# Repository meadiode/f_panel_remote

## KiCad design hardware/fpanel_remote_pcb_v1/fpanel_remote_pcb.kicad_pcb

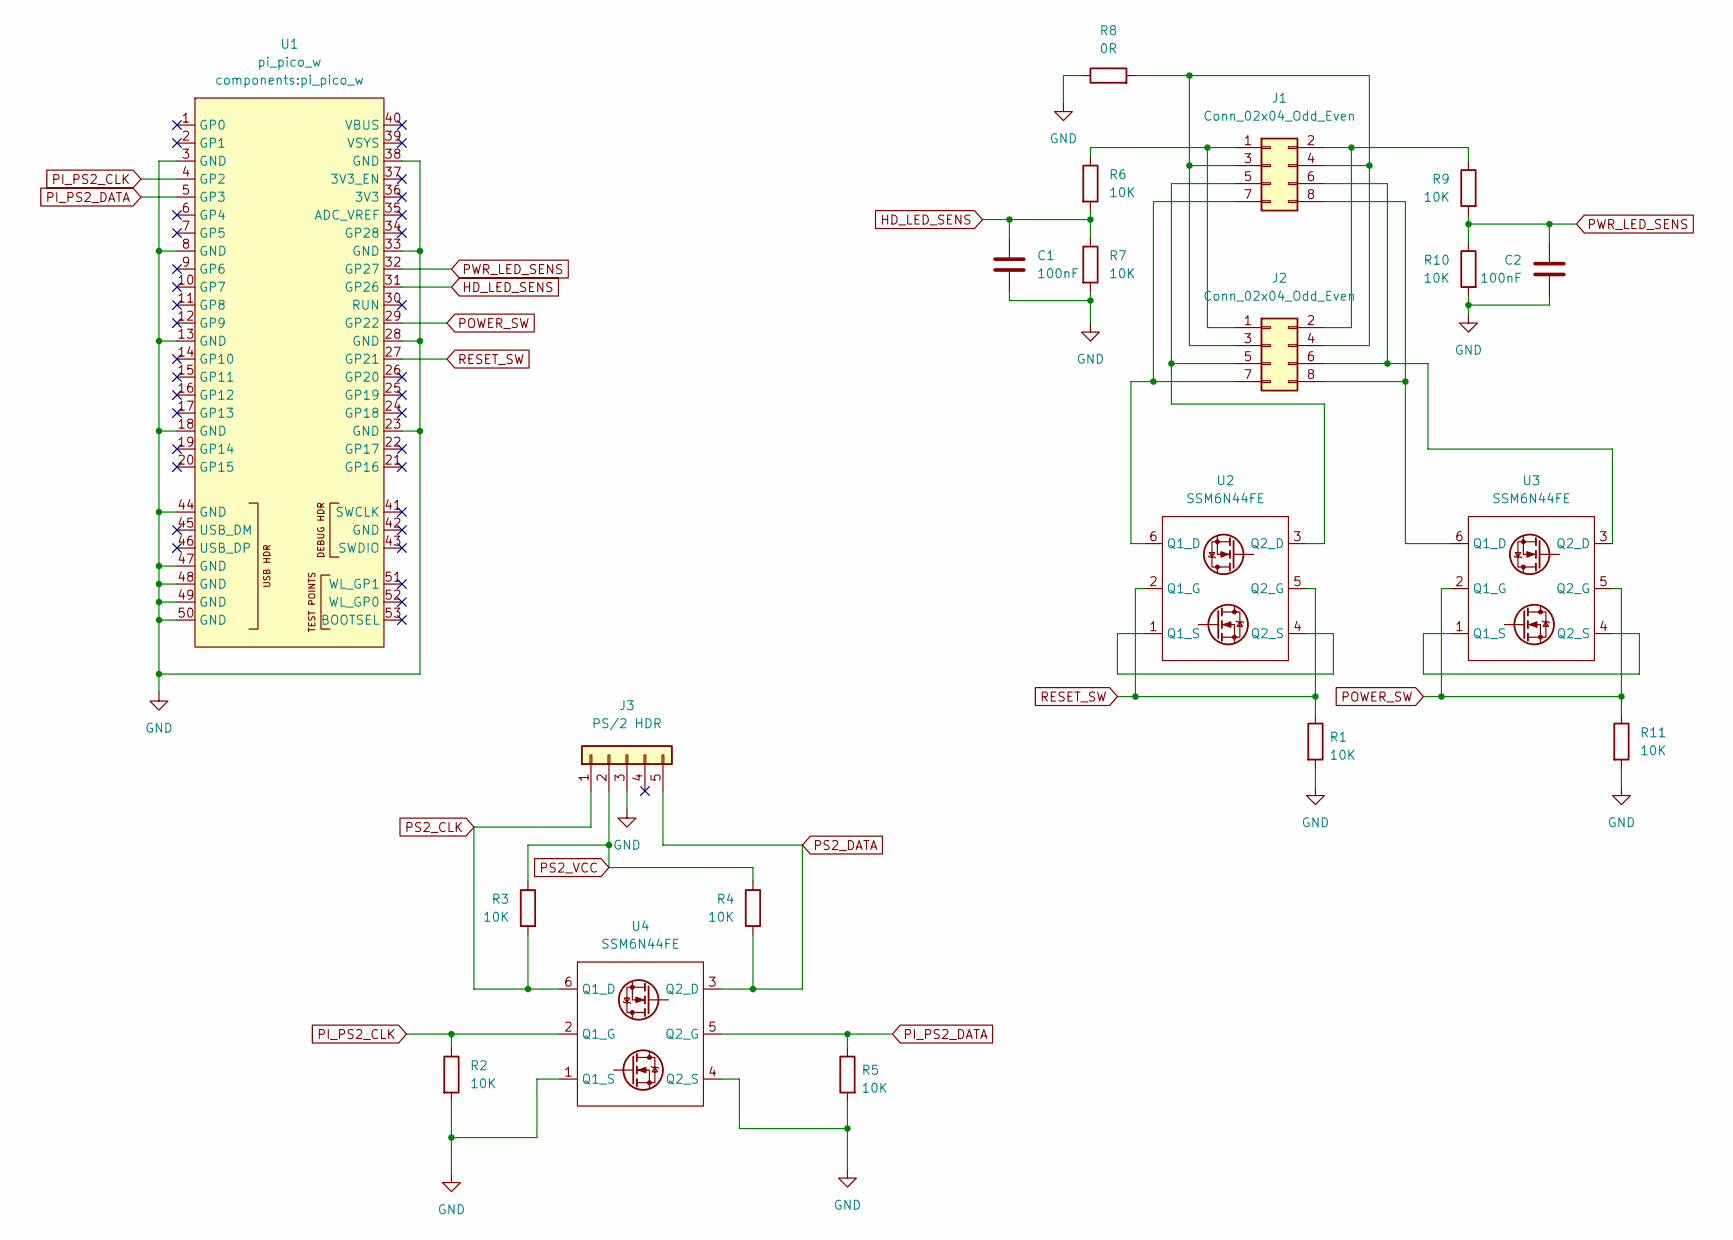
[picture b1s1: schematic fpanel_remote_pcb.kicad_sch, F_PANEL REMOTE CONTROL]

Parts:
C1, C2: 100nF; C_0603_1608Metric
J1, J2: Conn_02x04_Odd_Even; PinHeader_2x04_P2.54mm_Vertical
J3: PS/2 HDR; PinHeader_1x05_P2.54mm_Vertical
R1, R2, R3, R4, R5, R6, R7, R9, R10, R11: 10K; R_0603_1608Metric
R8: 0R; R_0603_1608Metric
U1: pi_pico_w
U2, U3, U4: SSM6N44FE; SOT-563

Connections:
GND: C1.2, C2.2, J3.3, R1.2, R2.2, R5.2, R7.2, R8.1, R10.2, R11.2, U1.3 (GND), U1.8 (GND), U1.13 (GND), U1.18 (GND), U1.23 (GND), U1.28 (GND), U1.33 (GND), U1.38 (GND), U1.44 (GND), U1.47 (GND), U1.48 (GND), U1.49 (GND), U1.50 (GND), U4.1 (Q1_S), U4.4 (Q2_S)
HD_LED_SENS: C1.1, R6.2, R7.1, U1.31 (GP26)
unnamed: J1.1, J2.1, R6.1
unnamed: J1.2, J2.2, R9.1
unnamed: J1.3, J1.4, J2.3, J2.4, R8.2
unnamed: J1.5, J2.5, U2.3 (Q2_D)
unnamed: J1.6, J2.6, U3.3 (Q2_D)
unnamed: J1.7, J2.7, U2.6 (Q1_D)
unnamed: J1.8, J2.8, U3.6 (Q1_D)
unnamed: U2.1 (Q1_S), U2.4 (Q2_S)
unnamed: U3.1 (Q1_S), U3.4 (Q2_S)
PI_PS2_CLK: R2.1, U1.4 (GP2), U4.2 (Q1_G)
PI_PS2_DATA: R5.1, U1.5 (GP3), U4.5 (Q2_G)
POWER_SW: R11.1, U1.29 (GP22), U3.2 (Q1_G), U3.5 (Q2_G)
PS2_CLK: J3.1, R3.2, U4.6 (Q1_D)
PS2_DATA: J3.5, R4.2, U4.3 (Q2_D)
PS2_VCC: J3.2, R3.1, R4.1
PWR_LED_SENS: C2.1, R9.2, R10.1, U1.32 (GP27)
RESET_SW: R1.1, U1.27 (GP21), U2.2 (Q1_G), U2.5 (Q2_G)

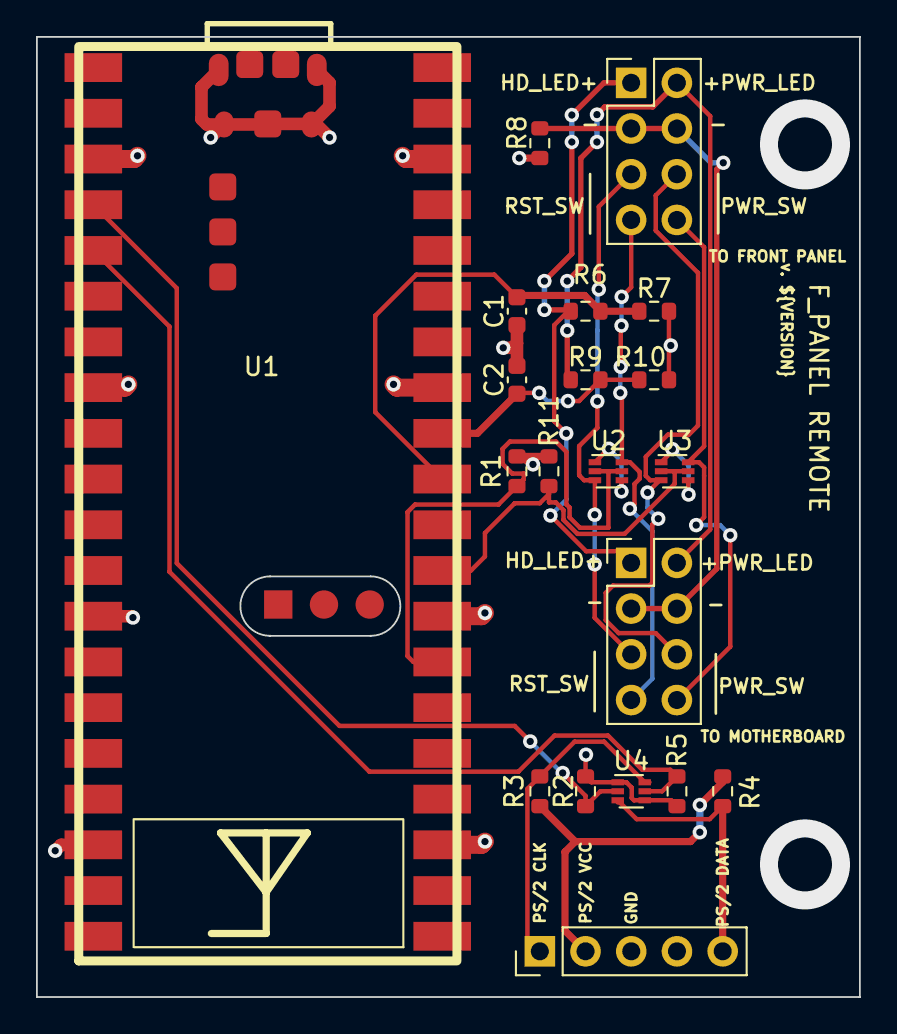
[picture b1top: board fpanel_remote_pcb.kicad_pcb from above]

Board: 2 copper layers, 45.7 x 53.3 mm, 20 parts (0 on the bottom side), 19 nets.

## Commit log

2023-05-03 fix pcb and schematics
2023-10-12 update pcb - minor changes

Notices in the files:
hardware/fpanel_remote_pcb_v1/fpanel_remote_pcb.kicad_pcb:
COOLHORSE INDUSTRIES (C) 2023
